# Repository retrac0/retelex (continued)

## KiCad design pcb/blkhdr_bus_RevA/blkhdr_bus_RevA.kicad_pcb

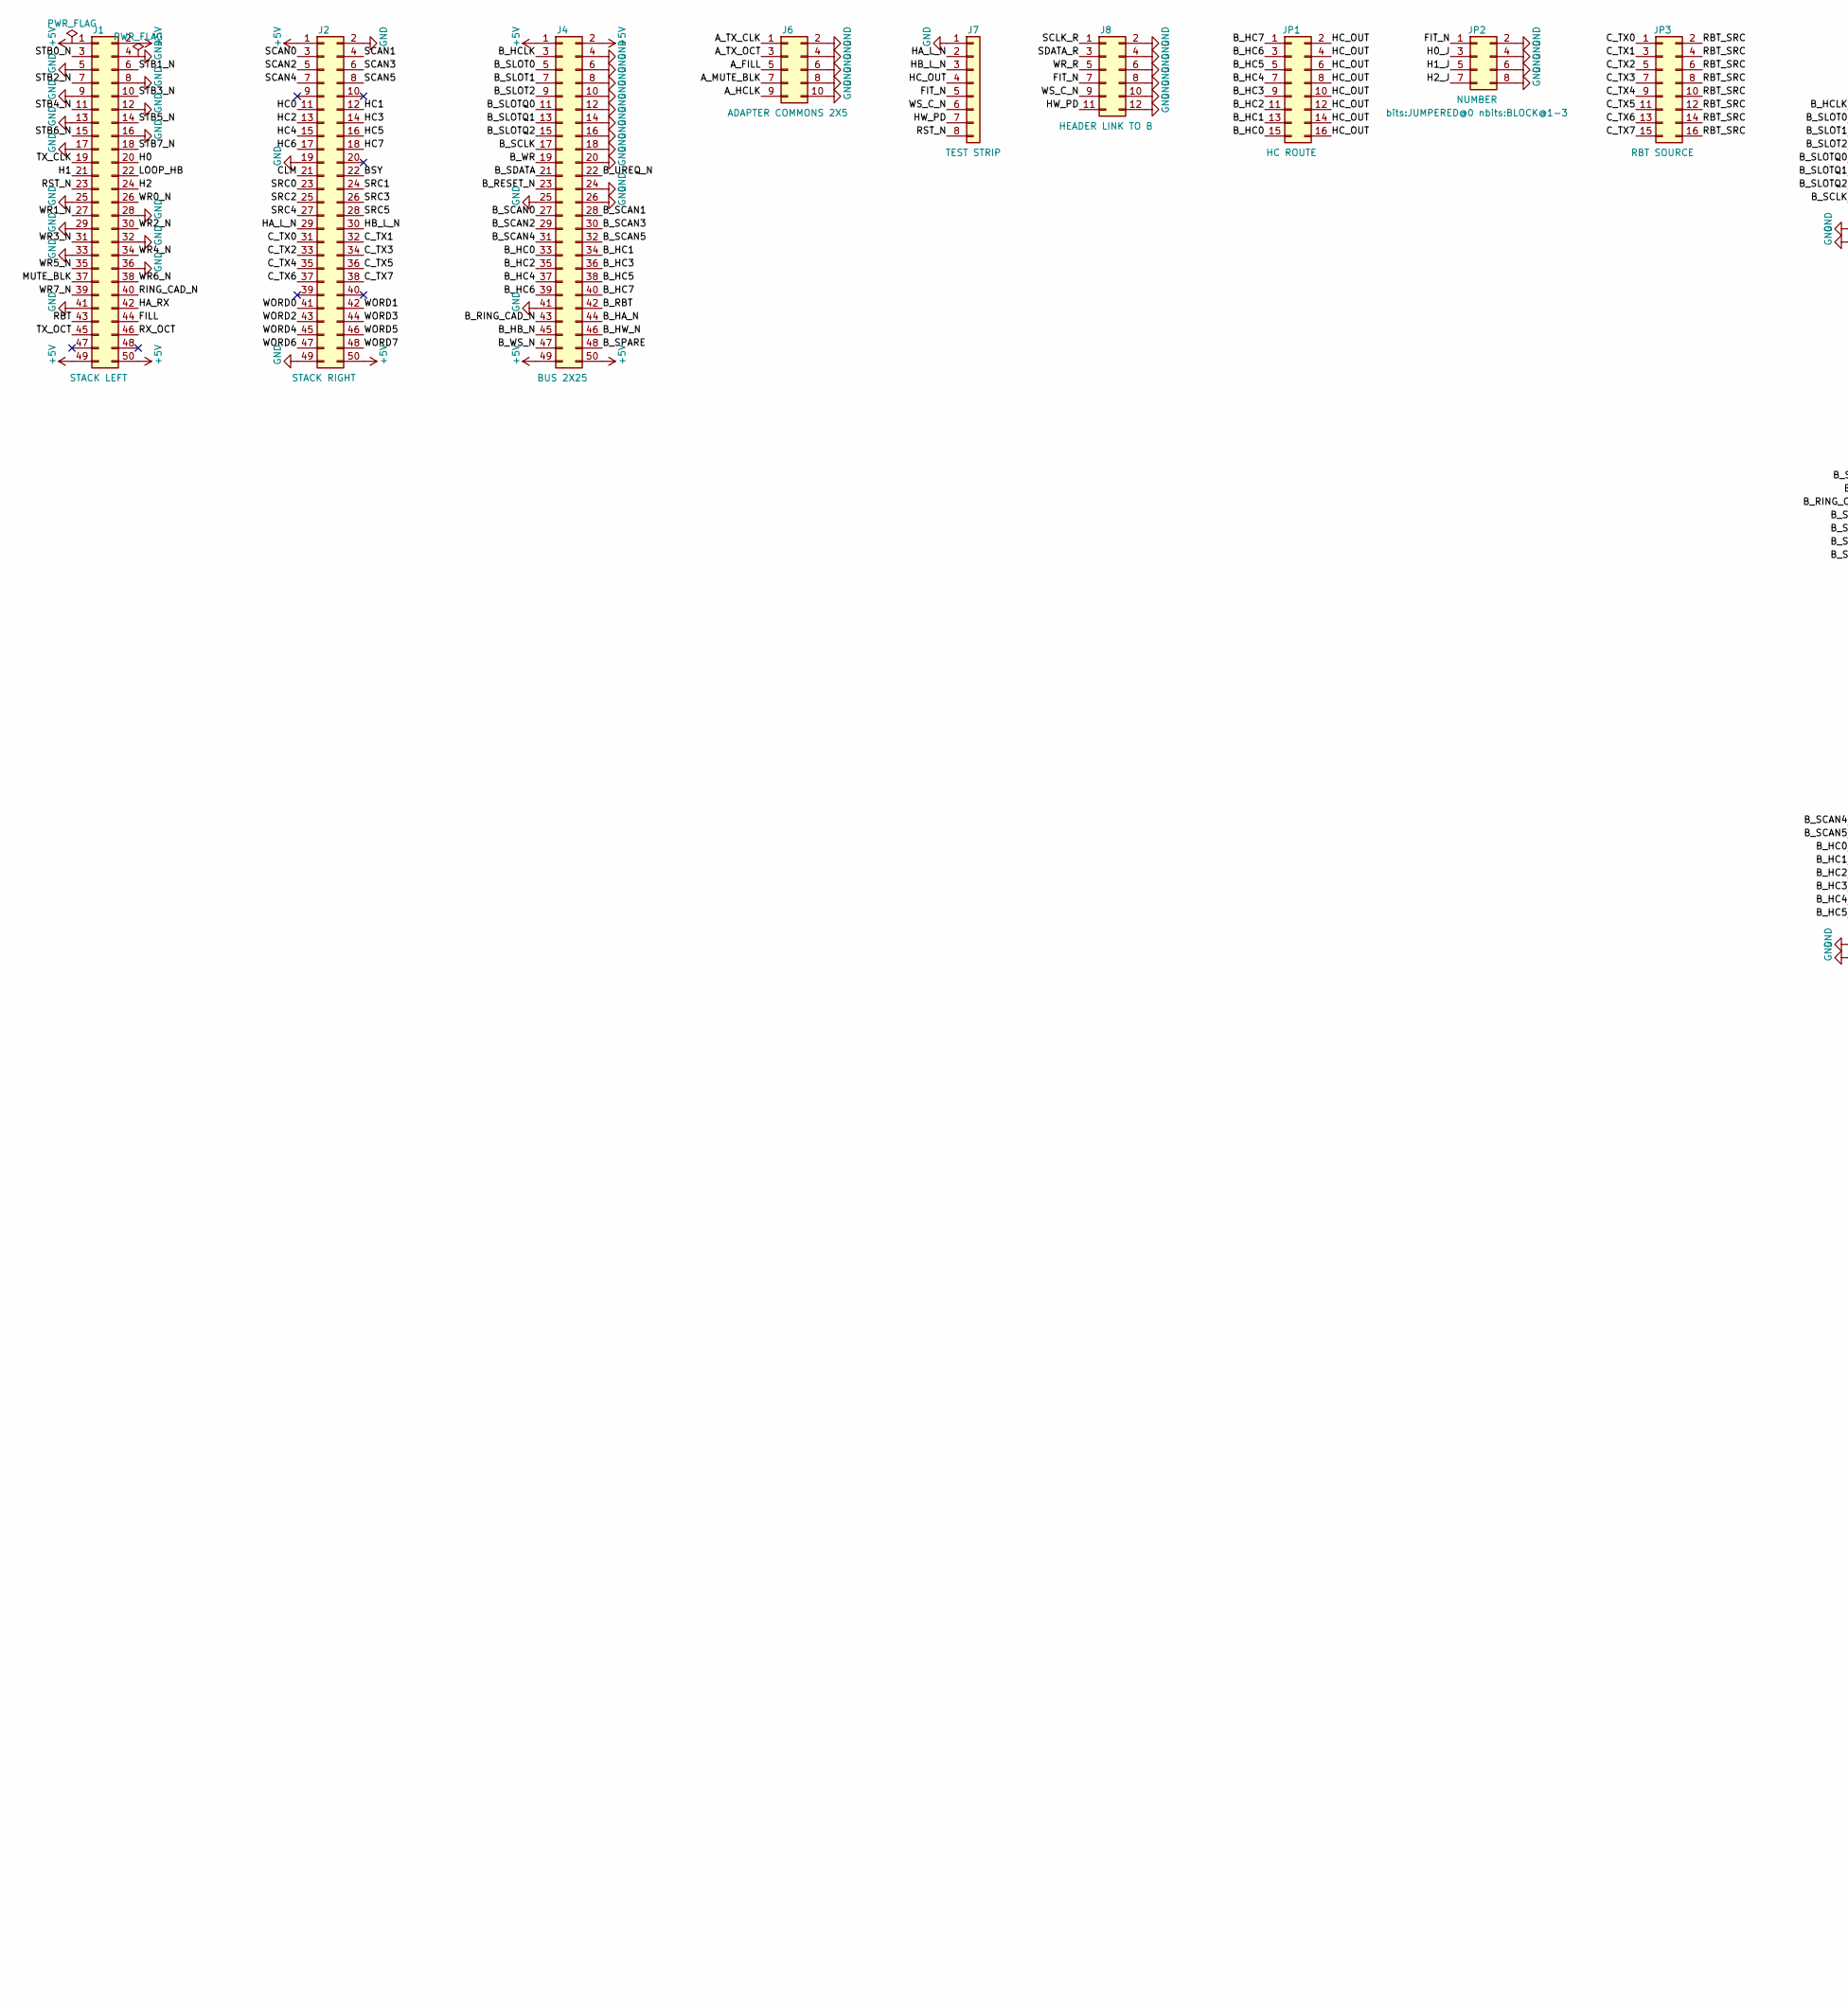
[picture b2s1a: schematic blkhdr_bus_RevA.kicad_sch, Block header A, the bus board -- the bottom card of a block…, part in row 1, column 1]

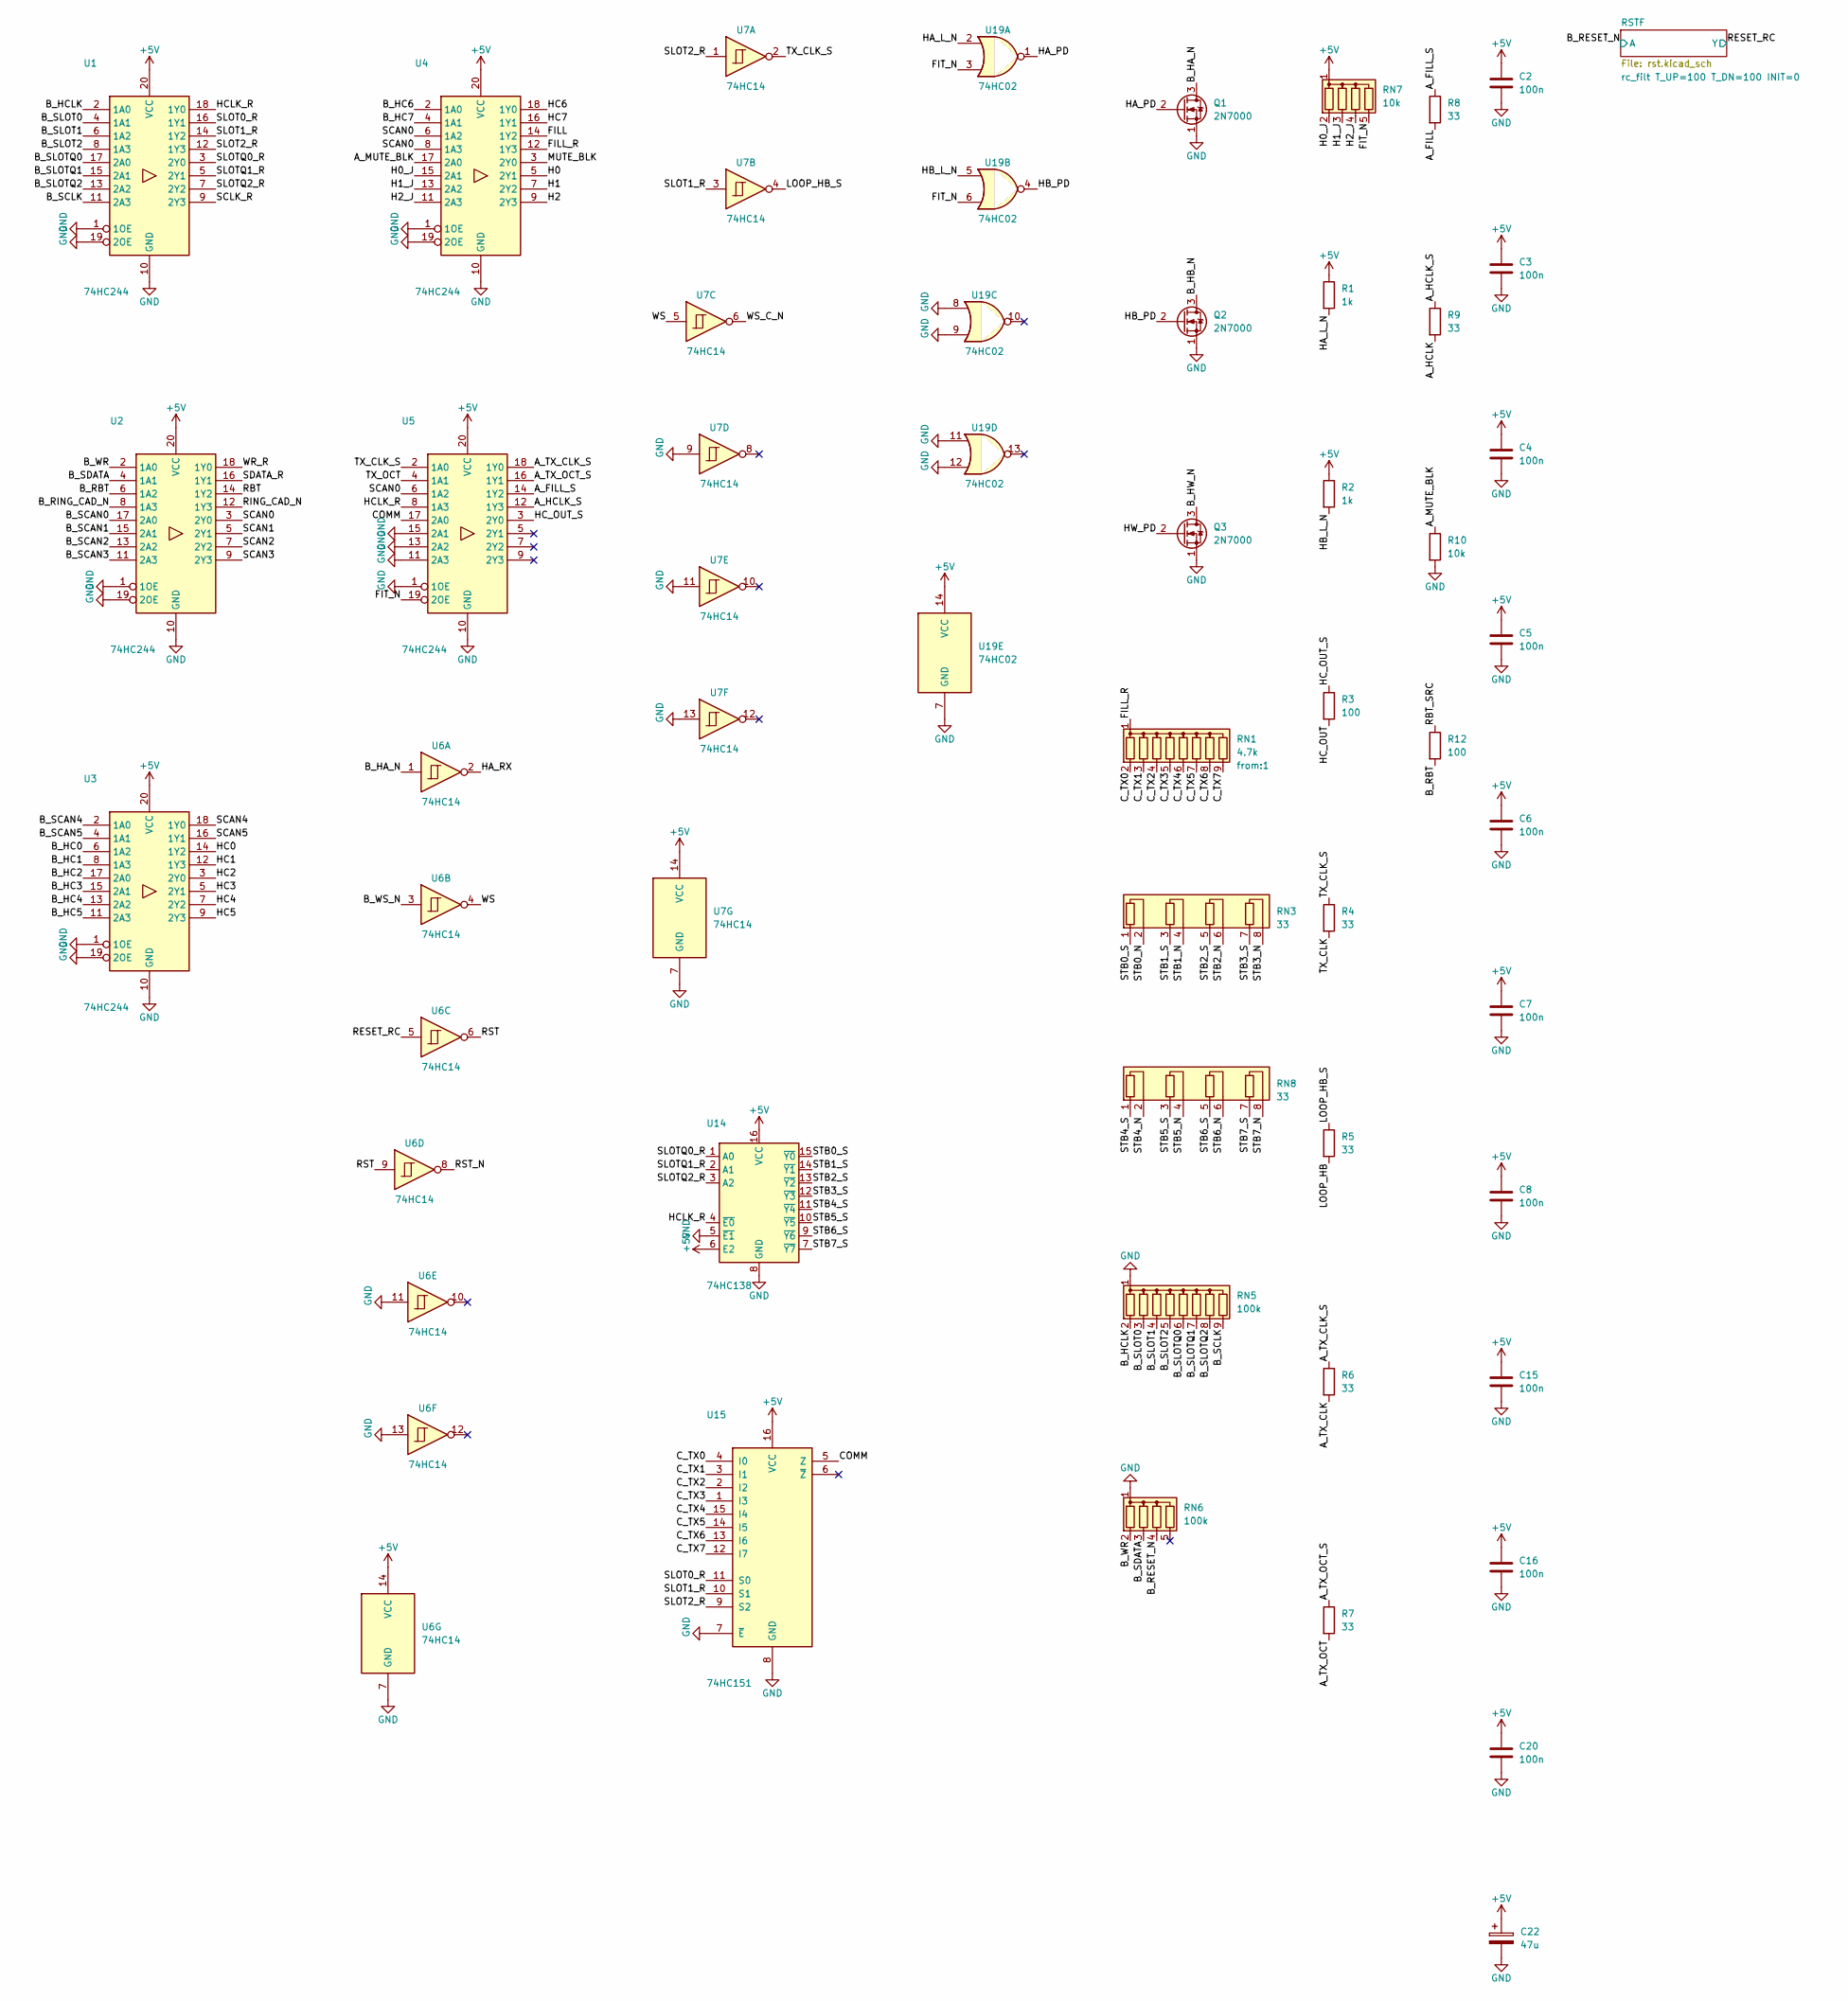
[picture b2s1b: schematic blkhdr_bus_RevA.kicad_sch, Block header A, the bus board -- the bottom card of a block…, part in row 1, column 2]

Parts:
C2, C3, C4, C5, C6, C7, C8, C15, C16, C20: 100n; C_Disc_D3.0mm_W1.6mm_P2.50mm
C22: 47u; CP_Radial_D4.0mm_P1.50mm
J1: STACK LEFT; PinSocket_2x25_P2.54mm_Vertical
J2: STACK RIGHT; PinSocket_2x25_P2.54mm_Vertical
J4: BUS 2X25; IDC-Header_2x25_P2.54mm_Horizontal
J6: ADAPTER COMMONS 2X5; IDC-Header_2x05_P2.54mm_Horizontal
J7: TEST STRIP; PinHeader_1x08_P2.54mm_Horizontal
J8: HEADER LINK TO B; PinSocket_2x06_P2.54mm_Vertical
JP1: HC ROUTE; PinHeader_2x08_P2.54mm_Vertical
JP2: NUMBER; PinHeader_2x04_P2.54mm_Vertical
JP3: RBT SOURCE; PinHeader_2x08_P2.54mm_Vertical
Q1, Q2, Q3: 2N7000; TO-92_Inline
R1, R2: 1k; R_Axial_DIN0207_L6.3mm_D2.5mm_P2.54mm_Vertical
R3, R12: 100; R_Axial_DIN0207_L6.3mm_D2.5mm_P2.54mm_Vertical
R4, R5, R6, R7, R8, R9: 33; R_Axial_DIN0207_L6.3mm_D2.5mm_P2.54mm_Vertical
R10: 10k; R_Axial_DIN0207_L6.3mm_D2.5mm_P2.54mm_Vertical
RN1: 4.7k; R_Array_SIP9
RN3, RN8: 33; R_Array_SIP8
RN5: 100k; R_Array_SIP9
RN6: 100k; R_Array_SIP5
RN7: 10k; R_Array_SIP5
U1, U2, U3, U4, U5: 74HC244; DIP-20_W7.62mm
U6, U7: 74HC14; DIP-14_W7.62mm
U14: 74HC138; DIP-16_W7.62mm
U15: 74HC151; DIP-16_W7.62mm
U19: 74HC02; DIP-14_W7.62mm

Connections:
+5V: C2.1, C3.1, C4.1, C5.1, C6.1, C7.1, C8.1, C15.1, C16.1, C20.1, C22.1, J1.1, J1.2, J1.49, J1.50, J2.1, J2.50, J4.1, J4.2, J4.49, J4.50, R1.1, R2.1, RN7.1 (common), U1.20 (VCC), U2.20 (VCC), U3.20 (VCC), U4.20 (VCC), U5.20 (VCC), U6.14 (VCC), U7.14 (VCC), U14.6 (E2), U14.16 (VCC), U15.16 (VCC), U19.14 (VCC)
/A_FILL: J6.5, R8.2
/A_FILL_S: R8.1, U5.14 (1Y2)
/A_HCLK: J6.9, R9.2
/A_HCLK_S: R9.1, U5.12 (1Y3)
/A_MUTE_BLK: J6.7, R10.1, U4.17 (2A0)
/A_TX_CLK: J6.1, R6.2
/A_TX_CLK_S: R6.1, U5.18 (1Y0)
/A_TX_OCT: J6.3, R7.2
/A_TX_OCT_S: R7.1, U5.16 (1Y1)
/BSY: J2.22
/B_HA_N: J4.44, Q1.3 (D), U6.1
/B_HB_N: J4.45, Q2.3 (D)
/B_HC0: J4.33, JP1.15, U3.6 (1A2)
/B_HC1: J4.34, JP1.13, U3.8 (1A3)
/B_HC2: J4.35, JP1.11, U3.17 (2A0)
/B_HC3: J4.36, JP1.9, U3.15 (2A1)
/B_HC4: J4.37, JP1.7, U3.13 (2A2)
/B_HC5: J4.38, JP1.5, U3.11 (2A3)
/B_HC6: J4.39, JP1.3, U4.2 (1A0)
/B_HC7: J4.40, JP1.1, U4.4 (1A1)
/B_HCLK: J4.3, RN5.2 (R1), U1.2 (1A0)
/B_HW_N: J4.46, Q3.3 (D)
/B_RBT: J4.42, R12.2, U2.6 (1A2)
/B_RESET_N: J4.23, RN6.4 (R3); also elsewhere on the board
/B_RING_CAD_N: J4.43, U2.8 (1A3)
/B_SCAN0: J4.27, U2.17 (2A0)
/B_SCAN1: J4.28, U2.15 (2A1)
/B_SCAN2: J4.29, U2.13 (2A2)
/B_SCAN3: J4.30, U2.11 (2A3)
/B_SCAN4: J4.31, U3.2 (1A0)
/B_SCAN5: J4.32, U3.4 (1A1)
/B_SCLK: J4.17, RN5.9 (R8), U1.11 (2A3)
/B_SDATA: J4.21, RN6.3 (R2), U2.4 (1A1)
/B_SLOT0: J4.5, RN5.3 (R2), U1.4 (1A1)
/B_SLOT1: J4.7, RN5.4 (R3), U1.6 (1A2)
/B_SLOT2: J4.9, RN5.5 (R4), U1.8 (1A3)
/B_SLOTQ0: J4.11, RN5.6 (R5), U1.17 (2A0)
/B_SLOTQ1: J4.13, RN5.7 (R6), U1.15 (2A1)
/B_SLOTQ2: J4.15, RN5.8 (R7), U1.13 (2A2)
/B_SPARE: J4.48
/B_UREQ_N: J4.22
/B_WR: J4.19, RN6.2 (R1), U2.2 (1A0)
/B_WS_N: J4.47, U6.3
/CLM: J2.21
/COMM: U5.17 (2A0), U15.5 (Z)
/C_TX0: J2.31, JP3.1, RN1.2 (R1), U15.4 (I0)
/C_TX1: J2.32, JP3.3, RN1.3 (R2), U15.3 (I1)
/C_TX2: J2.33, JP3.5, RN1.4 (R3), U15.2 (I2)
/C_TX3: J2.34, JP3.7, RN1.5 (R4), U15.1 (I3)
/C_TX4: J2.35, JP3.9, RN1.6 (R5), U15.15 (I4)
/C_TX5: J2.36, JP3.11, RN1.7 (R6), U15.14 (I5)
/C_TX6: J2.37, JP3.13, RN1.8 (R7), U15.13 (I6)
/C_TX7: J2.38, JP3.15, RN1.9 (R8), U15.12 (I7)
/FILL: J1.44, U4.14 (1Y2)
/FILL_R: RN1.1 (common), U4.12 (1Y3)
/FIT_N: J7.5, J8.7, JP2.1, RN7.5 (R4), U5.19 (2OE), U19.3, U19.6
/H0: J1.20, U4.5 (2Y1)
/H0_J: JP2.3, RN7.2 (R1), U4.15 (2A1)
/H1: J1.21, U4.7 (2Y2)
/H1_J: JP2.5, RN7.3 (R2), U4.13 (2A2)
/H2: J1.24, U4.9 (2Y3)
/H2_J: JP2.7, RN7.4 (R3), U4.11 (2A3)
/HA_L_N: J2.29, J7.2, R1.2, U19.2
/HA_PD: Q1.2 (G), U19.1
/HA_RX: J1.42, U6.2
/HB_L_N: J2.30, J7.3, R2.2, U19.5
/HB_PD: Q2.2 (G), U19.4
/HC0: J2.11, U3.14 (1Y2)
/HC1: J2.12, U3.12 (1Y3)
/HC2: J2.13, U3.3 (2Y0)
/HC3: J2.14, U3.5 (2Y1)
/HC4: J2.15, U3.7 (2Y2)
/HC5: J2.16, U3.9 (2Y3)
/HC6: J2.17, U4.18 (1Y0)
/HC7: J2.18, U4.16 (1Y1)
/HCLK_R: U1.18 (1Y0), U5.8 (1A3), U14.4 (~E0)
/HC_OUT: J7.4, JP1.2, JP1.4, JP1.6, JP1.8, JP1.10, JP1.12, JP1.14, JP1.16, R3.2
/HC_OUT_S: R3.1, U5.3 (2Y0)
/HW_PD: J7.7, J8.11, Q3.2 (G)
/LOOP_HB: J1.22, R5.2
/LOOP_HB_S: R5.1, U7.4
/MUTE_BLK: J1.37, U4.3 (2Y0)
/RBT: J1.43, U2.14 (1Y2)
/RBT_SRC: JP3.2, JP3.4, JP3.6, JP3.8, JP3.10, JP3.12, JP3.14, JP3.16, R12.1
/RESET_RC: U6.5; also elsewhere on the board
/RING_CAD_N: J1.40, U2.12 (1Y3)
/RST: U6.6, U6.9
/RST_N: J1.23, J7.8, U6.8
/RX_OCT: J1.46
/SCAN0: J2.3, U2.3 (2Y0), U4.6 (1A2), U4.8 (1A3), U5.6 (1A2)
/SCAN1: J2.4, U2.5 (2Y1)
/SCAN2: J2.5, U2.7 (2Y2)
/SCAN3: J2.6, U2.9 (2Y3)
/SCAN4: J2.7, U3.18 (1Y0)
/SCAN5: J2.8, U3.16 (1Y1)
/SCLK_R: J8.1, U1.9 (2Y3)
/SDATA_R: J8.3, U2.16 (1Y1)
/SLOT0_R: U1.16 (1Y1), U15.11 (S0)
/SLOT1_R: U1.14 (1Y2), U7.3, U15.10 (S1)
/SLOT2_R: U1.12 (1Y3), U7.1, U15.9 (S2)
/SLOTQ0_R: U1.3 (2Y0), U14.1 (A0)
/SLOTQ1_R: U1.5 (2Y1), U14.2 (A1)
/SLOTQ2_R: U1.7 (2Y2), U14.3 (A2)
/SRC0: J2.23
/SRC1: J2.24
/SRC2: J2.25
/SRC3: J2.26
/SRC4: J2.27
/SRC5: J2.28
/STB0_N: J1.3, RN3.2 (R1.2)
/STB0_S: RN3.1 (R1.1), U14.15 (~Y0)
/STB1_N: J1.6, RN3.4 (R2.2)
/STB1_S: RN3.3 (R2.1), U14.14 (~Y1)
/STB2_N: J1.7, RN3.6 (R3.2)
/STB2_S: RN3.5 (R3.1), U14.13 (~Y2)
/STB3_N: J1.10, RN3.8 (R4.2)
/STB3_S: RN3.7 (R4.1), U14.12 (~Y3)
/STB4_N: J1.11, RN8.2 (R1.2)
/STB4_S: RN8.1 (R1.1), U14.11 (~Y4)
/STB5_N: J1.14, RN8.4 (R2.2)
/STB5_S: RN8.3 (R2.1), U14.10 (~Y5)
/STB6_N: J1.15, RN8.6 (R3.2)
/STB6_S: RN8.5 (R3.1), U14.9 (~Y6)
/STB7_N: J1.18, RN8.8 (R4.2)
/STB7_S: RN8.7 (R4.1), U14.7 (~Y7)
/TX_CLK: J1.19, R4.2
/TX_CLK_S: R4.1, U5.2 (1A0), U7.2
/TX_OCT: J1.45, U5.4 (1A1)
/WORD0: J2.41
/WORD1: J2.42
/WORD2: J2.43
/WORD3: J2.44
/WORD4: J2.45
/WORD5: J2.46
/WORD6: J2.47
/WORD7: J2.48
/WR0_N: J1.26
/WR1_N: J1.27
/WR2_N: J1.30
/WR3_N: J1.31
/WR4_N: J1.34
/WR5_N: J1.35
/WR6_N: J1.38
/WR7_N: J1.39
/WR_R: J8.5, U2.18 (1Y0)
/WS: U6.4, U7.5
/WS_C_N: J7.6, J8.9, U7.6
GND: C2.2, C3.2, C4.2, C5.2, C6.2, C7.2, C8.2, C15.2, C16.2, C20.2, C22.2, J1.4, J1.5, J1.8, J1.9, J1.12, J1.13, J1.16, J1.17, J1.25, J1.28, J1.29, J1.32, J1.33, J1.36, J1.41, J2.2, J2.19, J2.49, J4.4, J4.6, J4.8, J4.10, J4.12, J4.14, J4.16, J4.18, J4.20, J4.24, J4.25, J4.26, J4.41, J6.2, J6.4, J6.6, J6.8, J6.10, J7.1, J8.2, J8.4, J8.6, J8.8, J8.10, J8.12, JP2.2, JP2.4, JP2.6, JP2.8, Q1.1 (S), Q2.1 (S), Q3.1 (S), R10.2, RN5.1 (common), RN6.1 (common), U1.1 (1OE), U1.10 (GND), U1.19 (2OE), U2.1 (1OE), U2.10 (GND), U2.19 (2OE), U3.1 (1OE), U3.10 (GND), U3.19 (2OE), U4.1 (1OE), U4.10 (GND), U4.19 (2OE), U5.1 (1OE), U5.10 (GND), U5.11 (2A3), U5.13 (2A2), U5.15 (2A1), U6.7 (GND), U6.11, U6.13, U7.7 (GND), U7.9, U7.11, U7.13, U14.5 (~E1), U14.8 (GND), U15.7 (~E), U15.8 (GND), U19.7 (GND), U19.8, U19.9, U19.11, U19.12; also elsewhere on the board

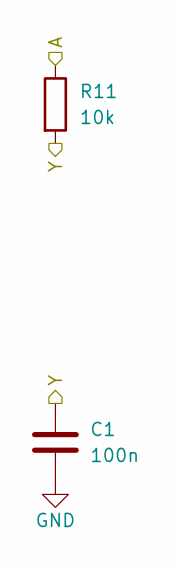
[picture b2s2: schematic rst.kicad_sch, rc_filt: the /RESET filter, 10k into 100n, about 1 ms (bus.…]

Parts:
C1: 100n; C_Disc_D5.0mm_W2.5mm_P2.50mm
R11: 10k; R_Axial_DIN0207_L6.3mm_D2.5mm_P2.54mm_Vertical

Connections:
/B_RESET_N: R11.1; also elsewhere on the board
/RESET_RC: C1.1, R11.2; also elsewhere on the board
GND: C1.2; also elsewhere on the board

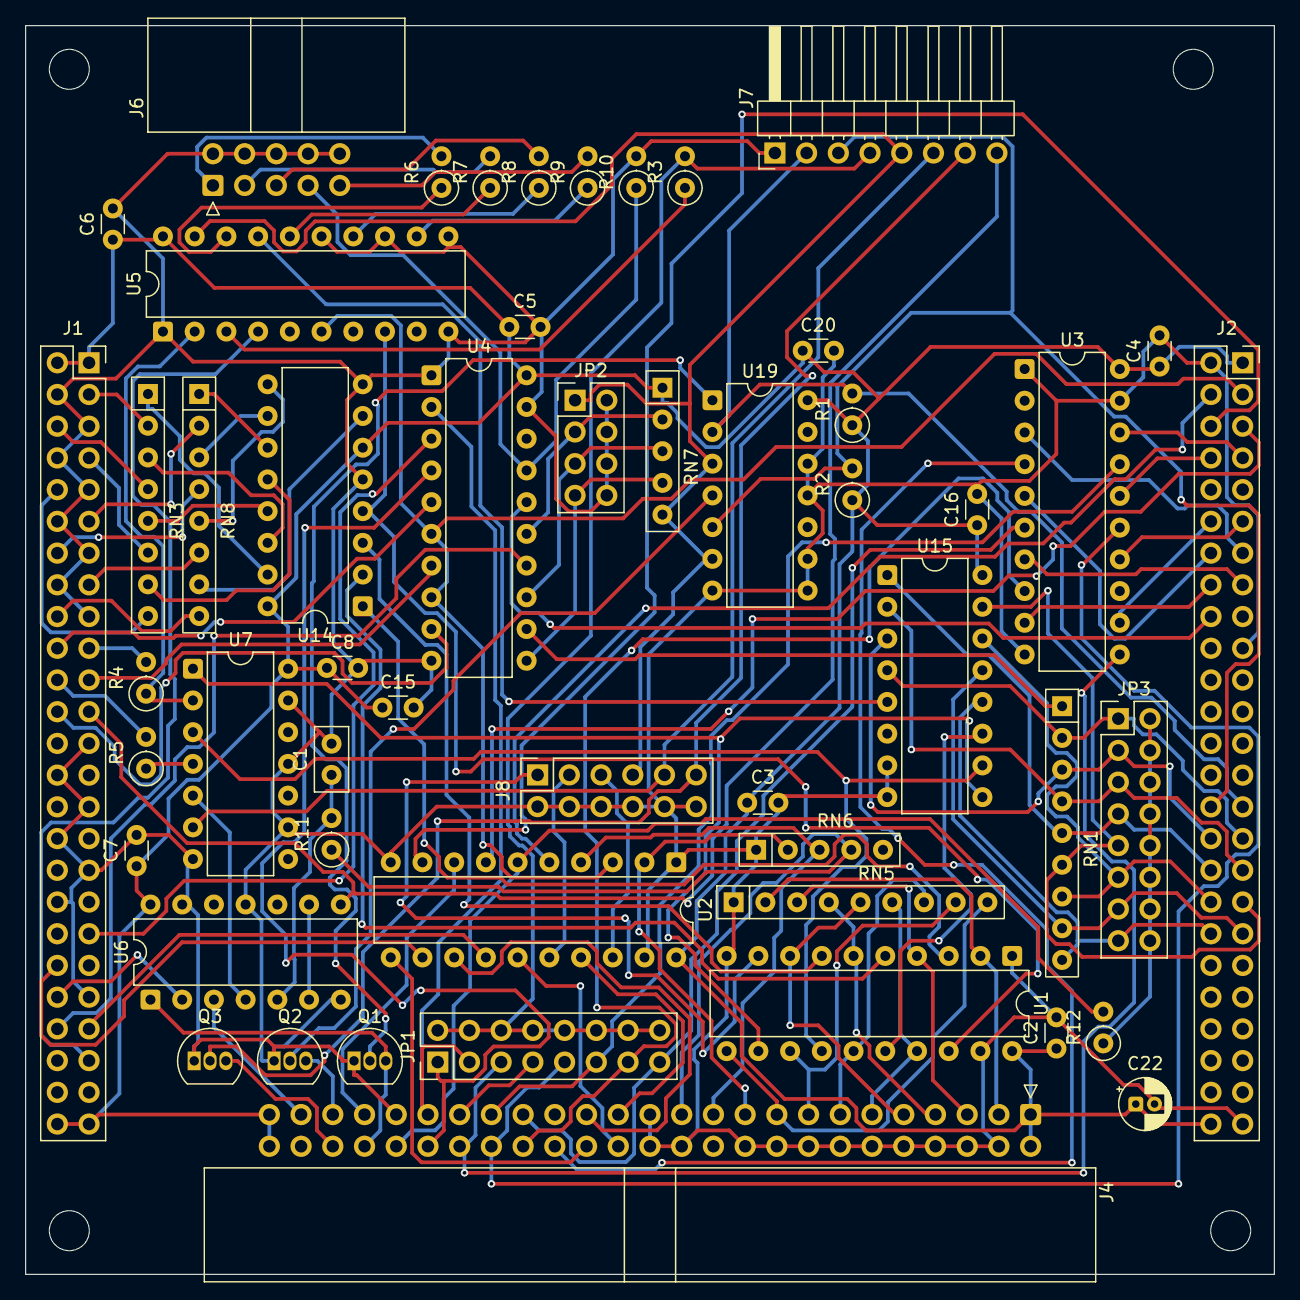
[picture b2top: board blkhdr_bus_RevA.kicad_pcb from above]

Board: 2 copper layers, 100.0 x 100.0 mm, 56 parts (0 on the bottom side), 122 nets.

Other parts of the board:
H1, H2, H3, H4: M3; MountingHole_3.2mm_M3
